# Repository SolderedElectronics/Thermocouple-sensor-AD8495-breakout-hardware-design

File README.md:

# Thermocouple sensor AD8495 breakout Hardware Design

## About the Product

|  |
| :----------------------------------------------------------: |
| [Buy Thermocouple sensor AD8495 breakout](https://www.solde.red/333053) |

<INSERT PRODUCT DESCRIPTION>

---

## Repository Contents

This repository contains all design files for Thermocouple sensor AD8495 breakout, organized as follows:

- **`CAD` folder**: Contains KiCAD design files, including:
  - Schematics
  - PCB layout
  - Panel PCB layout
  - Source 3D files in Fusion360, if any
  - All files are sorted by version with a detailed change log.
- **`OUTPUTS` folder**: Includes all production-ready files, such as:
  - Bill of Materials (BOM) and interactive BOM (iBOM)
  - PDF versions of schematics
  - 3D `.step` file of the board
  - 3D-printable models
  - Gerber files for PCB manufacturing
  - Image of the pinout of the board
  - Product image
  - Compliance, legal and generic sales documents

Refer to the `Change Log` in the CAD folder for details about updates between versions.

---

## Learn More About the Product

Beyond the repository, explore the following resources:

### Soldered Verify

The **Soldered Verify** system ensures every board you purchase from Soldered is fully functional. It also provides access to exclusive test data for your product. To get started, find the unique Soldered Verify ID on your product's packaging and enter the ID on the [Soldered Verify page](https://soldered.com/verify/) to access test results and additional product details.

### Soldered Community

Soldered Community is your go-to place for technical support. Our engineers track and answer all questions posted there, and it’s a great space for the maker community. Get answers to your questions and solutions for your challenges at [Soldered Community](https://soldered.com/community).

### solde.red

solde.red is an ultimate URL shortener and information hub. Access it by typing solde.red/ followed by your product SKU, e.g., [solde.red/333000](https://solde.red/333000), to find getting-started guides, datasheets, open-source hardware and software files, certifications, images, pinouts, and more. Read more about the shortener [here](https://solde.red/info/).

---

## Contributing

Contributions are welcome! Here’s how you can get involved:

- Submit pull requests to enhance the design or fix issues.
- Report bugs or problems by opening an issue.

We encourage community collaboration to make this product even better.

---

## About Soldered

[Soldered for Makers](https://soldered.com) specializes in designing and manufacturing electronic products tailored for enthusiasts, ranging from hobbyists to professionals. Our portfolio includes electronic boards, sensors, and actuators that are widely utilized in fields such as microelectronics, mechatronics, robotics, programming, and IoT. Every product we offer is designed in-house and built upon open-source hardware and software platforms. Proudly certified and manufactured within the European Union, our catalog likely includes the product you need for your project.

We complement these products with comprehensive tutorials and manuals, product descriptions, schematics, programming codes, and project examples. Our round-the-clock [customer and technical support](https://soldered.com/community) is available for all our products, irrespective of the sales channel. Soldered’s success and services reflect our maker community’s unwavering [trust](https://www.trustpilot.com/review/soldered.com), for which we are deeply grateful. Join our community and create using Soldered products.

---

## License

All Soldered open-source hardware (OSH) is under The TAPR Open Hardware License. Read more in the LICENSE file located in this repository.

**Disclaimer:**

No warranty - all designs in this repository are distributed in the hope that they will be useful, but without any warranty. They are provided "AS IS", therefore without warranty of any kind, either expressed or implied. The entire quality and performance of what you do with the contents of this repository are your responsibility. In no event Soldered Electronics will be liable for your damages, or losses, including any general, special, incidental, or consequential damage arising out of the use or inability to use the contents of this repository. 

---

## Have fun!

Thank you for your support from your fellow makers at Soldered Electronics.

Happy Making!

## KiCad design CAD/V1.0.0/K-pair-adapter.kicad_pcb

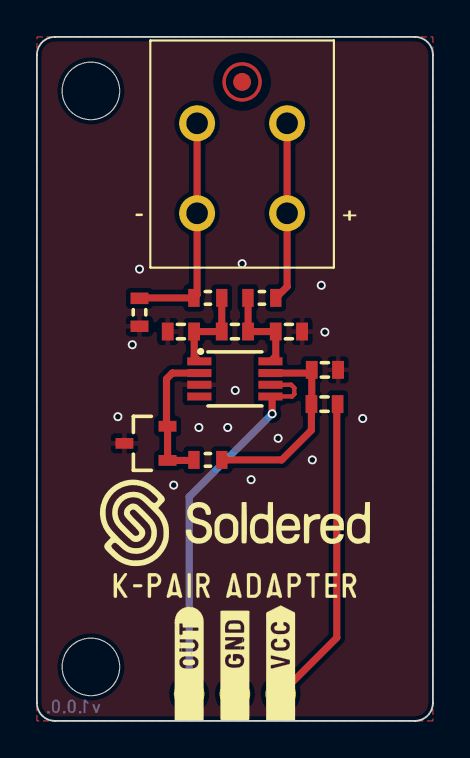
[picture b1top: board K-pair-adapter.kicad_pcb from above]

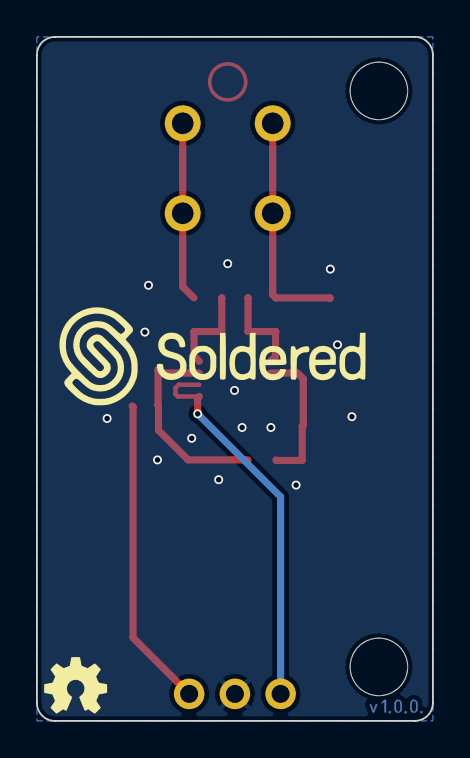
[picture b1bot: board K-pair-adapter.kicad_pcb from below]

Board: 2 copper layers, 22.0 x 38.0 mm, 17 parts (2 on the bottom side), 9 nets.

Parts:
C1, C3: 0.01uF; 0603C
C2, C4: 0.1uF; 0603C
FD1: FIDUCIAL; FIDUCIAL_23
H1, H2: HOLE_3.2mm
K1: TERMINAL_KF235-5.0-2P
K2: HEADER_MALE_3X1
L1: Ferrite bead; 0603L
R1: 1M; 0603R
R2, R3: 100R; 0603R
R4: 1K; 0603R
Ref**: Val**; Version1.0.0.
U1: TL431ACDBZ; SOT-23-3
U2: AD8495ARMZ; TP4056M-MSOP8

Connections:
GND: C1.2, C3.1, C4.2, K2.2, R1.1, U1.3 (A), U2.3 (-Vs)
unnamed: C1.1, C2.2, R2.2, U2.8 (+IN)
unnamed: C2.1, C3.2, R3.2, U2.1 (-IN)
unnamed: K1.1, R1.2, R3.1
unnamed: K1.2, R2.1
unnamed: K2.1, U2.5 (SEN), U2.6 (OUT)
unnamed: K2.3, L1.1
unnamed: R4.1, U1.1 (C), U1.2 (REF), U2.2 (REF)
VCC: C4.1, L1.2, R4.2, U2.7 (+Vs)

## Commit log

2022-08-06 Updating open source files.
